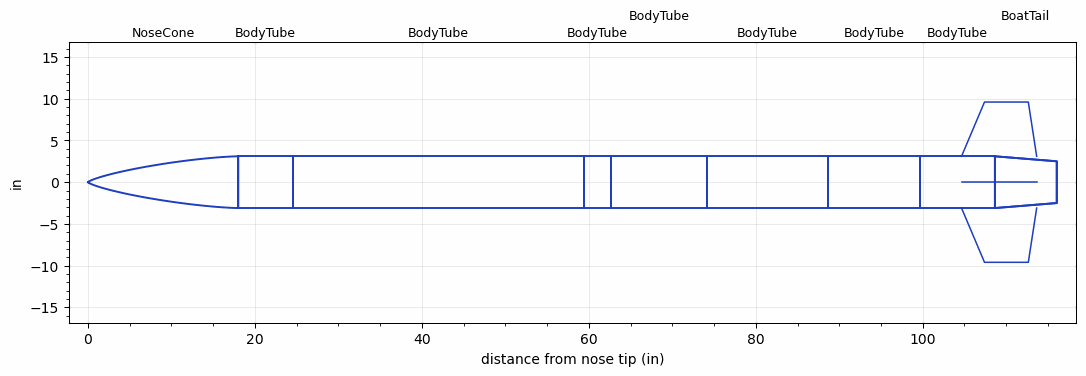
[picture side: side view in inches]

<RASAeroDocument>
 <FileVersion>2</FileVersion>
 <RocketDesign>
  <NoseCone>
   <Length>18</Length>
   <Diameter>6.2</Diameter>
   <Shape>Von Karman Ogive</Shape>
   <Location>0</Location>
  </NoseCone>
  <BodyTube>
   <Length>6.5</Length>
   <Diameter>6.2</Diameter>
   <Location>18</Location>
  </BodyTube>
  <BodyTube>
   <Length>34.8999</Length>
   <Diameter>6.2</Diameter>
   <Location>24.5</Location>
  </BodyTube>
  <BodyTube>
   <Length>3.25</Length>
   <Diameter>6.2</Diameter>
   <Location>59.3999</Location>
  </BodyTube>
  <BodyTube>
   <Length>11.5</Length>
   <Diameter>6.2</Diameter>
   <Location>62.6499</Location>
  </BodyTube>
  <BodyTube>
   <Length>14.5</Length>
   <Diameter>6.2</Diameter>
   <Location>74.1499</Location>
  </BodyTube>
  <BodyTube>
   <Length>11</Length>
   <Diameter>6.2</Diameter>
   <RailGuideDiameter>0.621</RailGuideDiameter>
   <RailGuideHeight>0.684</RailGuideHeight>
   <Location>88.6499</Location>
  </BodyTube>
  <BodyTube>
   <Length>9</Length>
   <Diameter>6.2</Diameter>
   <Location>99.6499</Location>
   <BoattailLength>7.41</BoattailLength>
   <BoattailRearDiameter>5</BoattailRearDiameter>
   <Overhang>5</Overhang>
   <Fin>
    <Count>4</Count>
    <Chord>9</Chord>
    <Span>6.5</Span>
    <SweepDistance>2.75</SweepDistance>
    <TipChord>5.25</TipChord>
    <Thickness>0.187</Thickness>
    <Location>4</Location>
    <AirfoilSection>Rounded</AirfoilSection>
   </Fin>
  </BodyTube>
  <BoatTail>
   <Length>7.41</Length>
   <Diameter>6.2</Diameter>
   <RearDiameter>5</RearDiameter>
   <Location>108.6499</Location>
  </BoatTail>
  <Surface>Sheet Metal</Surface>
  <ModifiedBarrowman>False</ModifiedBarrowman>
  <Turbulence>False</Turbulence>
  <UseBooster1>False</UseBooster1>
  <UseBooster2>False</UseBooster2>
 </RocketDesign>
 <LaunchSite>
  <Altitude>2871</Altitude>
  <Pressure>28.9938</Pressure>
  <RodAngle>6</RodAngle>
  <RodLength>154.9997</RodLength>
  <Temperature>86</Temperature>
  <WindSpeed>1.5882</WindSpeed>
 </LaunchSite>
 <Recovery>
  <Altitude1>1476</Altitude1>
  <Altitude2>656.168</Altitude2>
  <DeviceType1>Parachute</DeviceType1>
  <DeviceType2>Parachute</DeviceType2>
  <Event1>True</Event1>
  <Event2>True</Event2>
  <Size1>95.9998</Size1>
  <Size2>35.9999</Size2>
  <EventType1>Altitude</EventType1>
  <EventType2>Apogee</EventType2>
  <CD1>1.35</CD1>
  <CD2>0</CD2>
 </Recovery>
 <SimulationList>
  <Simulation>
   <SustainerLaunchWt>67.2035</SustainerLaunchWt>
   <SustainerCG>71.4486</SustainerCG>
   <SustainerIgnitionDelay>0</SustainerIgnitionDelay>
   <Booster1SeparationDelay>0</Booster1SeparationDelay>
   <Booster1IgnitionDelay>0</Booster1IgnitionDelay>
   <IncludeBooster1>False</IncludeBooster1>
   <Booster2Delay>0</Booster2Delay>
   <IncludeBooster2>False</IncludeBooster2>
  </Simulation>
 </SimulationList>
</RASAeroDocument>
